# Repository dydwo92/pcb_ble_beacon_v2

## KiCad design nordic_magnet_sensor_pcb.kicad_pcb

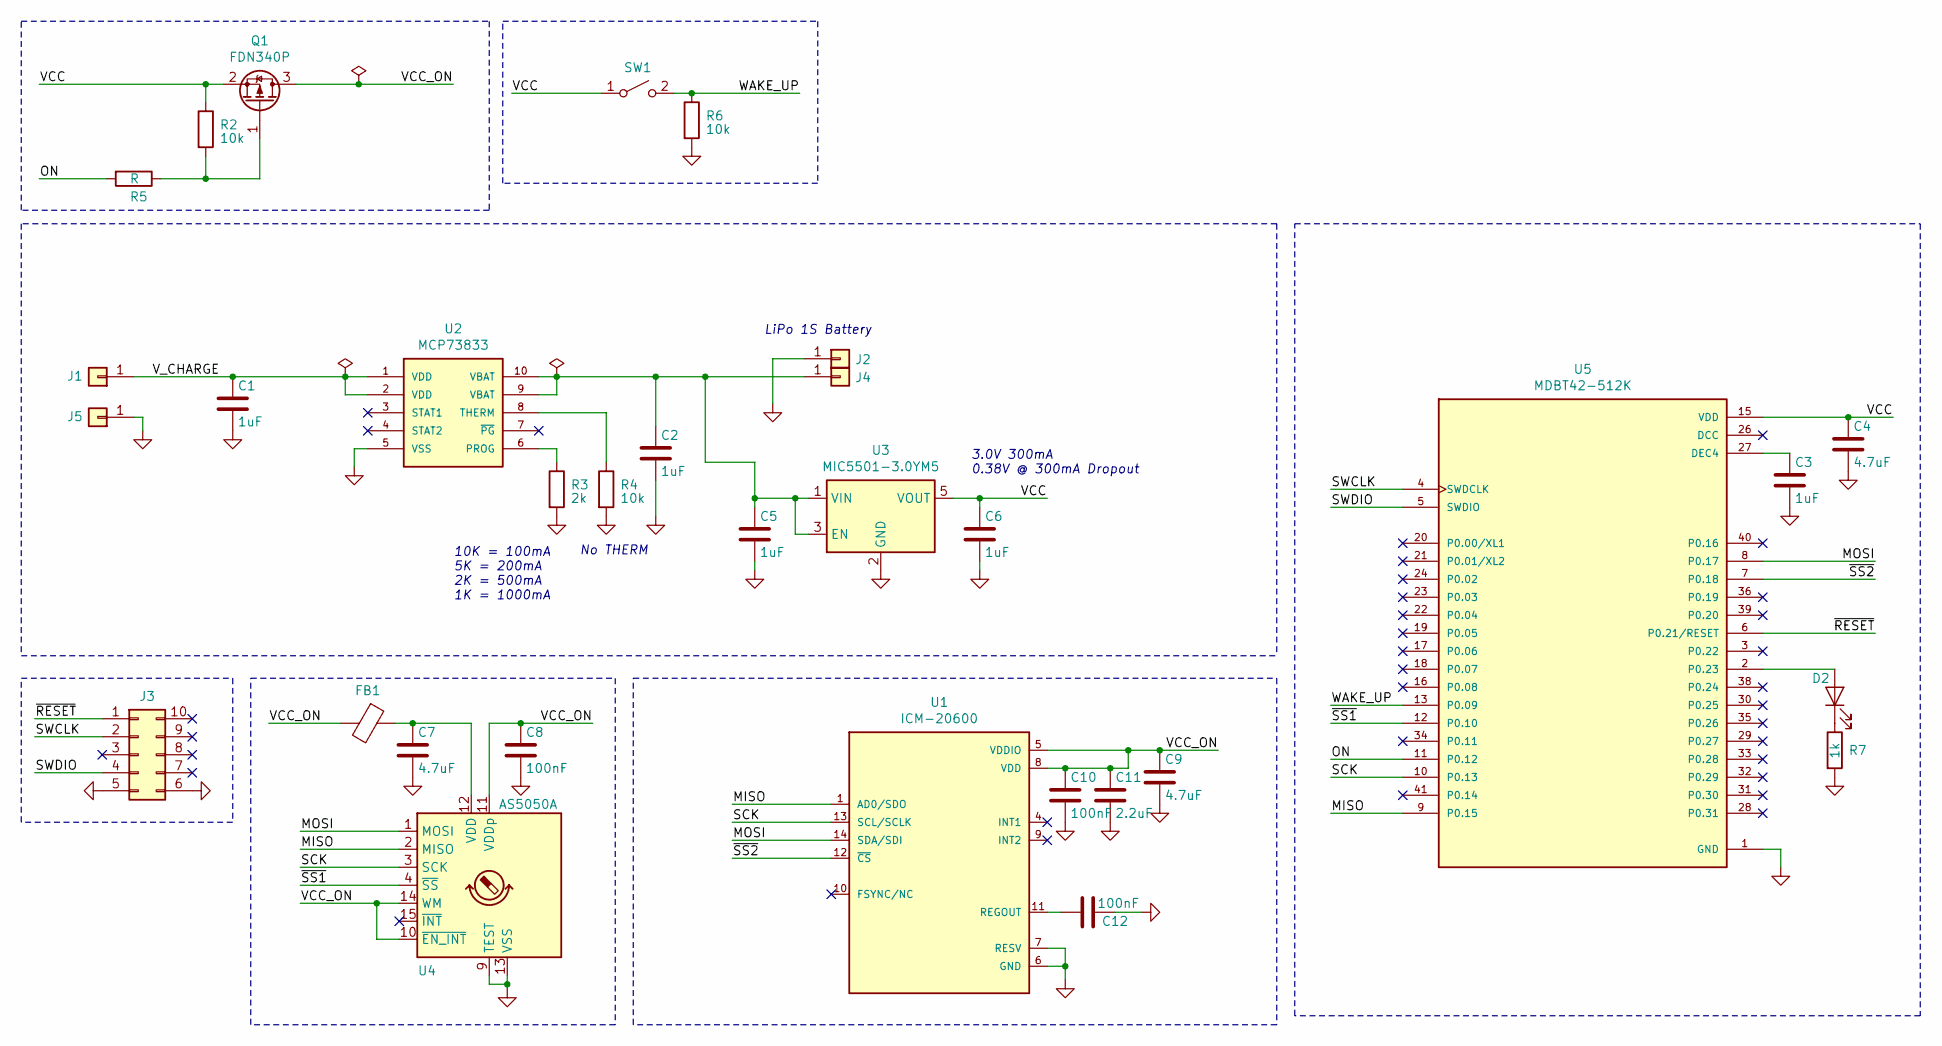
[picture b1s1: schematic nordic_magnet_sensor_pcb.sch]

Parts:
C1, C2: 1uF; C_0603_1608Metric
C3, C5, C6: 1uF; C_0402_1005Metric
C4: 4.7uF; C_0603_1608Metric
C7, C9: 4.7uF; C_0402_1005Metric
C8, C10, C12: 100nF; C_0402_1005Metric
C11: 2.2uF; C_0402_1005Metric
D2: LED; LED_0603_1608Metric
FB1: Ferrite_Bead; L_0603_1608Metric
J1, J5: Conn_01x01; 1578-3-57-15-00-00-03-0
J2, J4: Conn_01x01; TestPoint_Pad_D1.5mm
J3: Conn_02x05_Counter_Clockwise; Tag-Connect_TC2050-IDC-NL_2x05_P1.27mm_Vertical
Q1: FDN340P; SOT-23
R2, R4, R6: 10k; R_0402_1005Metric
R3: 2k; R_0402_1005Metric
R5: R; R_0402_1005Metric
R7: 1k; R_0603_1608Metric
SW1: SW_SPST; SW_SPST_B3U-1000P
U1: ICM-20600; PQFN50P250X300X97-14N
U2: MCP73833; MSOP-10_3x3mm_P0.5mm; Manufacture # MCP73833T-AMI/UN; DigiKey MCP73833T-AMI/UNCT-ND
U3: MIC5501-3.0YM5; SOT-23-5; Manufacture # MIC5501-3.0YM5-TR; DigiKey 576-4905-1-ND
U4: AS5050A; QFN-16-1EP_4x4mm_P0.65mm_EP2.7x2.7mm; Manufacture # AS5050A-BQFM; DigiKey AS5050A-BQFMCT-ND
U5: MDBT42-512K

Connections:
/MISO: U1.1 (AD0/SDO), U4.2 (MISO), U5.9 (P0.15)
/MOSI: U1.14 (SDA/SDI), U4.1 (MOSI), U5.8 (P0.17)
/ON: R5.2, U5.11 (P0.12)
/SCK: U1.13 (SCL/SCLK), U4.3 (SCK), U5.10 (P0.13)
/SWCLK: J3.2, U5.4 (SWDCLK)
/SWDIO: J3.4, U5.5 (SWDIO)
/VCC: C4.1, C6.1, Q1.2 (S), R2.1, SW1.1 (A), U3.5 (VOUT), U5.15 (VDD)
/VCC_ON: C8.1, C9.1, C10.1, C11.1, FB1.2, Q1.3 (D), U1.5 (VDDIO), U1.8 (VDD), U4.10 (~EN_INT), U4.11 (VDDp), U4.14 (WM)
/V_CHARGE: C1.1, J1.1, U2.1 (VDD), U2.2 (VDD)
/WAKE_UP: R6.1, SW1.2 (B), U5.13 (P0.09)
/~RESET: J3.1, U5.6 (P0.21/RESET)
/~SS1: U4.4 (~SS), U5.12 (P0.10)
/~SS2: U1.12 (~CS~), U5.7 (P0.18)
GND: C1.2, C2.2, C3.2, C4.2, C5.2, C6.2, C7.2, C8.2, C9.2, C10.2, C11.2, C12.1, J2.1, J3.5, J3.6, J5.1, R3.2, R4.2, R6.2, R7.2, U1.6 (GND), U1.7 (RESV), U2.5 (VSS), U3.2 (GND), U4.9 (TEST), U4.13 (VSS), U5.1 (GND), U5.14 (GND), U5.25 (GND), U5.37 (GND)
unnamed: C2.1, C5.1, J4.1, U2.9 (VBAT), U2.10 (VBAT), U3.1 (VIN), U3.3 (EN)
unnamed: C3.1, U5.27 (DEC4)
unnamed: C7.1, FB1.1, U4.12 (VDD)
unnamed: C12.2, U1.11 (REGOUT)
unnamed: D2.1 (K), R7.1
unnamed: D2.2 (A), U5.2 (P0.23)
unnamed: Q1.1 (G), R2.2, R5.1
unnamed: R3.1, U2.6 (PROG)
unnamed: R4.1, U2.8 (THERM)

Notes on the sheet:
10K = 100mA 5K = 200mA 2K = 500mA 1K = 1000mA
No THERM
LiPo 1S Battery
3.0V 300mA 0.38V @ 300mA Dropout

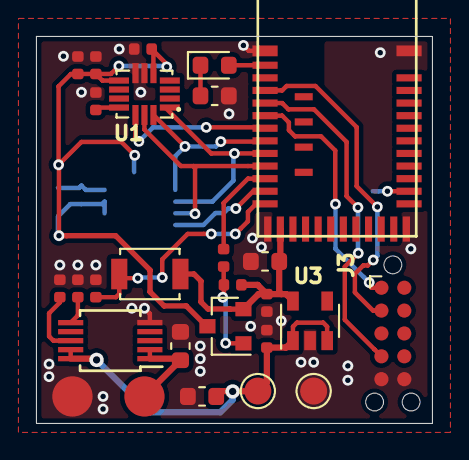
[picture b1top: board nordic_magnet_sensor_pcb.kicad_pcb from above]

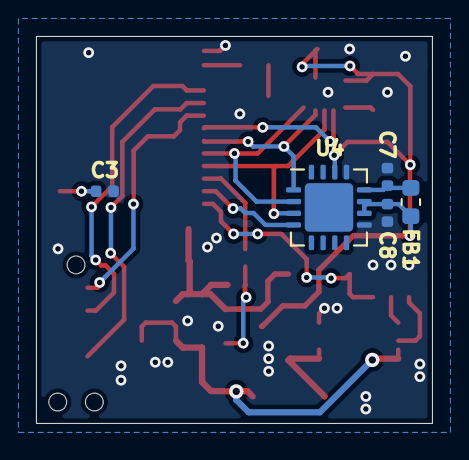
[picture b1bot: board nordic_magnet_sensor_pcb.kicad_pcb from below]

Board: 2 copper layers, 22.0 x 21.5 mm, 32 parts (5 on the bottom side), 23 nets.
